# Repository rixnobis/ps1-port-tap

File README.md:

# ps1-port-tap

A pass-through for one PlayStation controller or memory card port, with every line
broken out to a 0.1" header for a logic analyser. Cut a controller extension cable in
half, solder the console half to J1 and the device half to J2, and clip the analyser
onto J3.

## Why it is wired to a cut cable

The PS1 port connector is proprietary, and I could not find a published drawing of it
I would trust. The best public source is a forum post giving a 4 mm pitch, but its
author traced the positions from a scaled photo. So this revision has no connector on
the board: J1 and J2 are 1x10 rows at
2.54 mm with 1.0 mm holes, big enough for the cable's conductors. The M2 holes beside
each row are for zip ties that hold the cable jacket. A board-mounted socket can come
in a later revision, once someone has put calipers on a real one.

## Pinout

From psx-spx, `docs/ps1/pinouts/controller-ports-and-memory-card-ports.md`. Pins 1-9
are the port pins. Pin 10 carries the cable shield straight through and is not tapped.
Memory card slots have no IRQ (pin 8) and no shield.

| Pin | Signal | | Pin | Signal |
|---|---|---|---|---|
| 1 | DAT, data from device | | 6 | /CS, port select |
| 2 | CMD, data to device | | 7 | SCK, clock |
| 3 | +7.5V, rumble supply | | 8 | /IRQ, lightgun |
| 4 | GND | | 9 | /ACK, acknowledge |
| 5 | +3.5V, logic supply | | 10 | shield |

The full table is also printed on the back silkscreen, so the cable can be wired from
the board alone.

J3 is a 2x9 header. Odd pins carry the taps (DAT, CMD, 7V5, 3V5, CS, SCK, IRQ, ACK)
and every even pin is GND, so each probe gets its own ground. The signal taps go through
100R, which keeps the analyser's lead capacitance off the bus; fit 0R if you want a
transparent tap. The two supply taps go through 10k, so a probe clipped onto a rail
cannot short it.

## Layout

Two layers, 40 x 51 mm, routed by script and every run straight. Port line n crosses
B.Cu from J1 pin n to J2 pin n. A tapped line drops through a via at its J3 column and
runs straight down F.Cu to its resistor, and on to its J3 pin. Both layers are poured
with GND, with stitching vias between the through-lines, so the copper there stays as
stitched guard ground. The pour stops at a straight edge around each pad row, because
between two header pads it can only form slivers; the GND pins inside those strips reach
the pour through traces.

`tools/check_geometry.py` checks what DRC does not. It flags any bend sharper than
45 degrees, any segment shorter than its width, any trace narrower than its net class,
any dangling end and any overlapping segment. `tools/crops.sh` renders every pad row
and the resistor row at about 4x, in `renders/crops/`.

## Files

- `ps1-port-tap.kicad_sch`, `.kicad_pcb`, `.kicad_pro`: KiCad 10 project
- `schematic.pdf`, `renders/`: every copper and silk layer, plus 3D views
- `fab/ps1-port-tap-gerbers.zip`, `fab/ps1-port-tap-bom.csv`, `fab/ps1-port-tap-cpl.csv`:
  ready for JLCPCB, with the resistors assembled and the headers hand-fitted. On the
  JLC preview, check that the resistors sit square on their pads. LCSC lists C25804 (10k)
  as out of stock right now; any 0603 10k works.

## Rebuilding

Everything is generated from the scripts in `tools/`. `tools/build.sh` runs the whole
pipeline: schematic, ERC, placement and routing through the pcbnew Python API, pours,
DRC with schematic parity, the geometry check, renders, crops and fab outputs. It stops
on any ERC, DRC or geometry finding. Requires KiCad 10 (`kicad-cli` and the `pcbnew`
Python module), `rsvg-convert` and ImageMagick.

Not yet built or tested on hardware.

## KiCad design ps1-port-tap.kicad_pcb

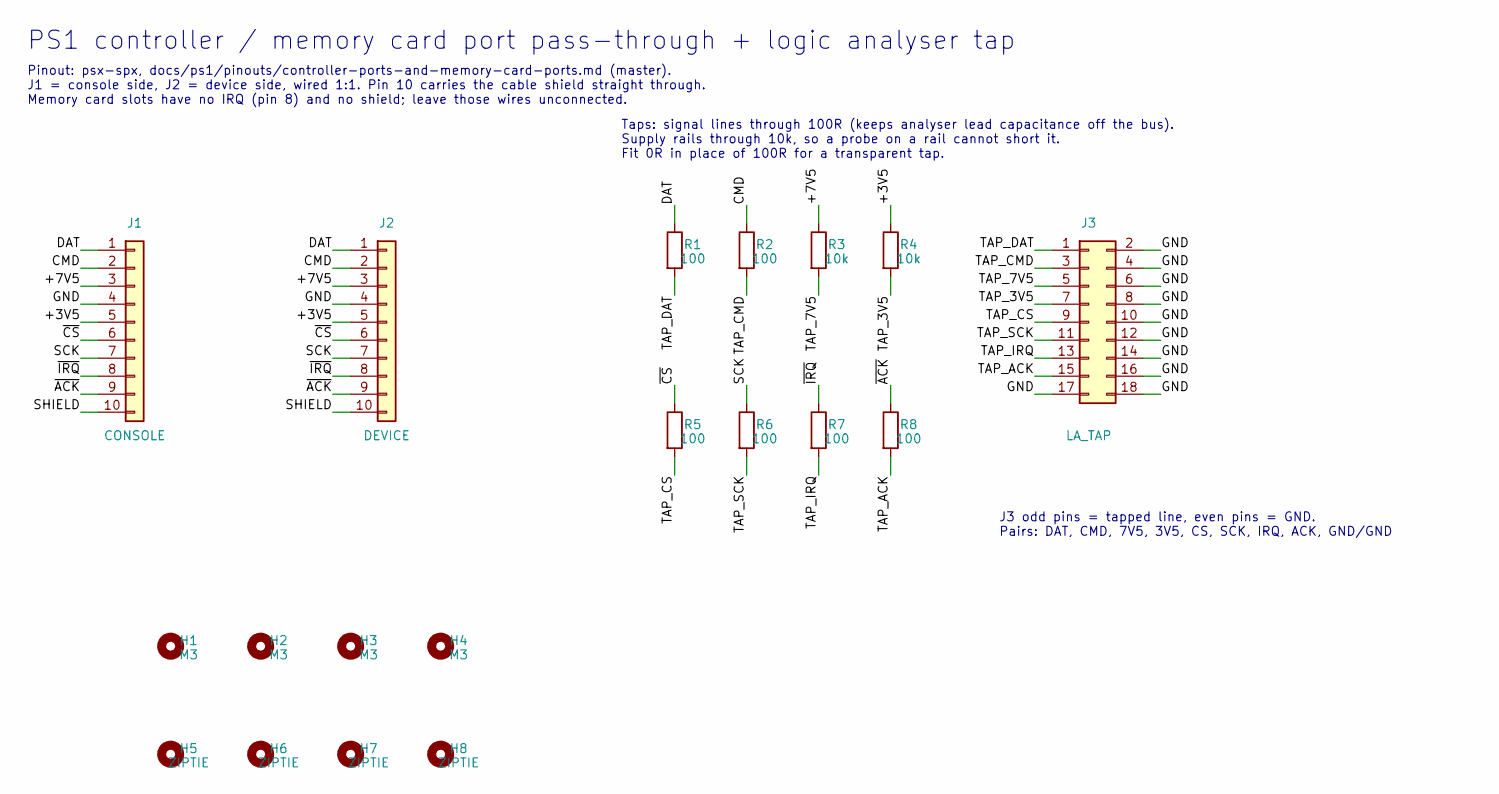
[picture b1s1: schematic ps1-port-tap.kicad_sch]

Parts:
H1, H2, H3, H4: M3; MountingHole_3.2mm_M3
H5, H6, H7, H8: ZIPTIE; MountingHole_2.2mm_M2
J1: CONSOLE; PinHeader_1x10_P2.54mm_Vertical
J2: DEVICE; PinHeader_1x10_P2.54mm_Vertical
J3: LA_TAP; PinHeader_2x09_P2.54mm_Vertical
R1, R2, R5, R6, R7, R8: 100; R_0603_1608Metric; LCSC C22775
R3, R4: 10k; R_0603_1608Metric; LCSC C25804

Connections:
/+3V5: J1.5, J2.5, R4.1
/+7V5: J1.3, J2.3, R3.1
/CMD: J1.2, J2.2, R2.1
/DAT: J1.1, J2.1, R1.1
/GND: J1.4, J2.4, J3.2, J3.4, J3.6, J3.8, J3.10, J3.12, J3.14, J3.16, J3.17, J3.18
/SCK: J1.7, J2.7, R6.1
/SHIELD: J1.10, J2.10
/TAP_3V5: J3.7, R4.2
/TAP_7V5: J3.5, R3.2
/TAP_ACK: J3.15, R8.2
/TAP_CMD: J3.3, R2.2
/TAP_CS: J3.9, R5.2
/TAP_DAT: J3.1, R1.2
/TAP_IRQ: J3.13, R7.2
/TAP_SCK: J3.11, R6.2
/~ACK: J1.9, J2.9, R8.1
/~CS: J1.6, J2.6, R5.1
/~IRQ: J1.8, J2.8, R7.1

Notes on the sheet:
PS1 controller / memory card port pass-through + logic analyser tap
Pinout: psx-spx, docs/ps1/pinouts/controller-ports-and-memory-card-ports.md (master). J1 = console side, J2 = device side, wired 1:1. Pin 10 carries the cable shield straight through. Memory card slots have no IRQ (pin 8) and no shield; leave those wires unconnected.
Taps: signal lines through 100R (keeps analyser lead capacitance off the bus). Supply rails through 10k, so a probe on a rail cannot short it. Fit 0R in place of 100R for a transparent tap.
J3 odd pins = tapped line, even pins = GND. Pairs: DAT, CMD, 7V5, 3V5, CS, SCK, IRQ, ACK, GND/GND

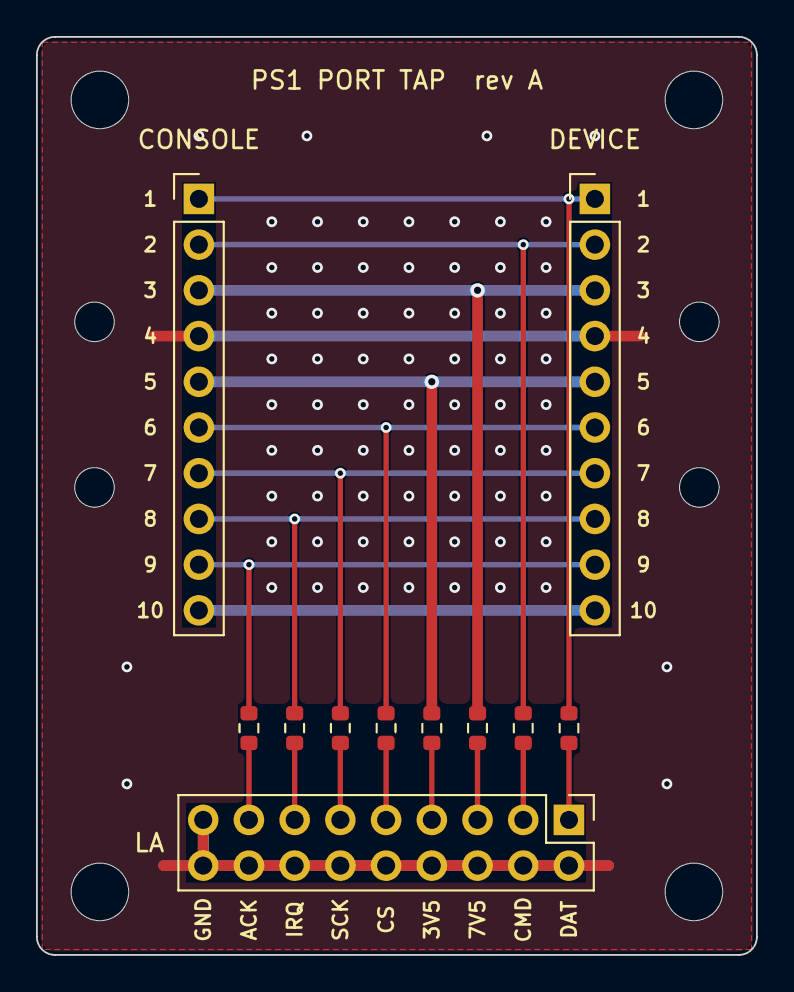
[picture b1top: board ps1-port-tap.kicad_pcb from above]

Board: 2 copper layers, 40.0 x 51.0 mm, 19 parts (0 on the bottom side), 18 nets.

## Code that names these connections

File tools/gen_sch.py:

#!/usr/bin/env python3
"""Generate ps1-port-tap.kicad_sch.

Symbols come from the stock KiCad library and are embedded in the file.
Every pin gets a short wire stub and a net label, so connectivity is carried
by label names rather than by drawn wires.
"""
import math
import re
import sys
import uuid as uuidlib
from pathlib import Path

SYMDIR = Path("/usr/share/kicad/symbols")
OUT = Path(__file__).resolve().parent.parent / "ps1-port-tap.kicad_sch"
ROOT_UUID = "6b1f3c2e-9a4d-4e57-8a0b-5f1d2c3e4a01"

# Port pinout: psx-spx, docs/ps1/pinouts/controller-ports-and-memory-card-ports.md
PORT = {
    1: "DAT",       # data from device (SIO0 RX)
    2: "CMD",       # data to device (SIO0 TX)
    3: "+7V5",      # rumble motor supply
    4: "GND",
    5: "+3V5",      # logic supply
    6: "~{CS}",     # port select
    7: "SCK",       # serial clock
    8: "~{IRQ}",    # lightgun IRQ, controller port only
    9: "~{ACK}",    # data acknowledge
    10: "SHIELD",   # cable shield, passed through, not tapped
}

# Tapped lines: (port pin, series resistor value)
TAPS = [
    (1, "100"), (2, "100"), (3, "10k"), (5, "10k"),
    (6, "100"), (7, "100"), (8, "100"), (9, "100"),
]


def uid():
    return str(uuidlib.uuid4())


def extract_symbol(lib, name):
    text = (SYMDIR / f"{lib}.kicad_sym").read_text()
    m = re.search(r'\n\t\(symbol "%s"\n' % re.escape(name), text)
    if not m:
        sys.exit(f"symbol {lib}:{name} not found")
    start = m.start() + 2  # skip "\n\t"
    depth = 0
    i = start
    in_str = False
    while True:
        c = text[i]
        if in_str:
            if c == "\\":
                i += 1
            elif c == '"':
                in_str = False
        elif c == '"':
            in_str = True
        elif c == "(":
            depth += 1
        elif c == ")":
            depth -= 1
            if depth == 0:
                break
        i += 1
    body = text[start:i + 1]
    assert body.startswith(f'(symbol "{name}"'), body[:60]
    body = body.replace(f'(symbol "{name}"', f'(symbol "{lib}:{name}"', 1)
    pins = {}
    for pm in re.finditer(
        r'\(pin \w+ \w+\s*\(at ([-\d.]+) ([-\d.]+) ([-\d.]+)\)\s*\(length [-\d.]+\)'
        r'(?:\s*\(hide yes\))?\s*\(name "[^"]*"(?:.|\n)*?\(number "([^"]+)"', body):
        x, y, a, num = float(pm[1]), float(pm[2]), float(pm[3]), pm[4]
        pins[num] = (x, y, a)
    return body, pins


LIBS = {
    "Conn_01x10": extract_symbol("Connector_Generic", "Conn_01x10"),
    "Conn_02x09_Odd_Even": extract_symbol("Connector_Generic", "Conn_02x09_Odd_Even"),
    "R": extract_symbol("Device", "R"),
    "MountingHole": extract_symbol("Mechanical", "MountingHole"),
}
LIBID = {
    "Conn_01x10": "Connector_Generic:Conn_01x10",
    "Conn_02x09_Odd_Even": "Connector_Generic:Conn_02x09_Odd_Even",
    "R": "Device:R",
    "MountingHole": "Mechanical:MountingHole",
}

items = []


def fmt(v):
    s = f"{v:.4f}".rstrip("0").rstrip(".")
    return "0" if s == "-0" else s


def place(kind, ref, value, footprint, x, y, nets, fields_extra=()):
    """nets: {pin_number: label}; a stub + label is drawn on each pin."""
    _, pins = LIBS[kind]
    su = uid()
    pin_uuids = "".join(f'\n\t\t(pin "{n}"\n\t\t\t(uuid "{uid()}")\n\t\t)' for n in pins)
    extra = "".join(
        f'\n\t\t(property "{k}" "{v}"\n\t\t\t(at {fmt(x)} {fmt(y)} 0)\n\t\t\t(effects\n\t\t\t\t(font\n\t\t\t\t\t(size 1.27 1.27)\n\t\t\t\t)\n\t\t\t\t(hide yes)\n\t\t\t)\n\t\t)'
        for k, v in fields_extra)
    in_bom = "no" if kind == "MountingHole" else "yes"
    items.append(f'''	(symbol
		(lib_id "{LIBID[kind]}")
		(at {fmt(x)} {fmt(y)} 0)
		(unit 1)
		(exclude_from_sim no)
		(in_bom {in_bom})
		(on_board yes)
		(dnp no)
		(uuid "{su}")
		(property "Reference" "{ref}"
			(at {fmt(x + (0 if kind.startswith('Conn') else 2.54))} {fmt(y - (14 if kind.startswith('Conn') else 0.8))} 0)
			(effects
				(font
					(size 1.27 1.27)
				)
			)
		)
		(property "Value" "{value}"
			(at {fmt(x + (0 if kind.startswith('Conn') else 2.54))} {fmt(y + (16 if kind.startswith('Conn') else 1.2))} 0)
			(effects
				(font
					(size 1.27 1.27)
				)
			)
		)
		(property "Footprint" "{footprint}"
			(at {fmt(x)} {fmt(y)} 0)
			(effects
				(font
					(size 1.27 1.27)
				)
				(hide yes)
			)
		)
		(property "Datasheet" ""
			(at {fmt(x)} {fmt(y)} 0)
			(effects
				(font
					(size 1.27 1.27)
				)
				(hide yes)
			)
		){extra}{pin_uuids}
		(instances
			(project "ps1-port-tap"
				(path "/{ROOT_UUID}"
					(reference "{ref}")
					(unit 1)
				)
			)
		)
	)''')
    for num, net in nets.items():
        px, py, a = pins[num]
        sx, sy = x + px, y - py                      # library y is up, sheet y is down
        dx, dy = -math.cos(math.radians(a)), math.sin(math.radians(a))
        ex, ey = sx + 2.54 * dx, sy + 2.54 * dy
        items.append(f'''	(wire
		(pts
			(xy {fmt(sx)} {fmt(sy)}) (xy {fmt(ex)} {fmt(ey)})
		)
		(stroke
			(width 0)
			(type default)
		)
		(uuid "{uid()}")
	)''')
        if abs(dx) > 0.5:
            ang, just = (180, "right") if dx < 0 else (0, "left")
        else:
            ang, just = (90, "left") if dy < 0 else (270, "right")
        items.append(f'''	(label "{net}"
		(at {fmt(ex)} {fmt(ey)} {ang})
		(effects
			(font
				(size 1.27 1.27)
			)
			(justify {just} bottom)
		)
		(uuid "{uid()}")
	)''')


def text(s, x, y, size=1.27):
    s = s.replace('"', '\\"').replace("\n", "\\n")  # no raw newlines inside a string
    items.append(f'''	(text "{s}"
		(exclude_from_sim no)
		(at {fmt(x)} {fmt(y)} 0)
		(effects
			(font
				(size {size} {size})
			)
			(justify left bottom)
		)
		(uuid "{uid()}")
	)''')


HDR1 = "Connector_PinHeader_2.54mm:PinHeader_1x10_P2.54mm_Vertical"
HDR2 = "Connector_PinHeader_2.54mm:PinHeader_2x09_P2.54mm_Vertical"
R0603 = "Resistor_SMD:R_0603_1608Metric"

place("Conn_01x10", "J1", "CONSOLE", HDR1, 40.64, 60.96, dict((str(k), v) for k, v in PORT.items()))
place("Conn_01x10", "J2", "DEVICE", HDR1, 76.2, 60.96, dict((str(k), v) for k, v in PORT.items()))

for i, (pin, val) in enumerate(TAPS):
    net = PORT[pin]
    tap = "TAP_" + re.sub(r"[~{}+]", "", net)
    place("R", f"R{i + 1}", val, R0603, 116.84 + 10.16 * (i % 4), 50.8 + 25.4 * (i // 4),
          {"1": net, "2": tap}, (("LCSC", "C22775" if val == "100" else "C25804"),))

hdr_nets = {}
for i, (pin, _) in enumerate(TAPS):
    hdr_nets[str(2 * i + 1)] = "TAP_" + re.sub(r"[~{}+]", "", PORT[pin])
    hdr_nets[str(2 * i + 2)] = "GND"
hdr_nets["17"] = "GND"
hdr_nets["18"] = "GND"
place("Conn_02x09_Odd_Even", "J3", "LA_TAP", HDR2, 175.26, 60.96, hdr_nets)

for i in range(4):
    place("MountingHole", f"H{i + 1}", "M3", "MountingHole:MountingHole_3.2mm_M3",
          45.72 + 12.7 * i, 106.68, {})
for i in range(4):
    place("MountingHole", f"H{i + 5}", "ZIPTIE", "MountingHole:MountingHole_2.2mm_M2",
          45.72 + 12.7 * i, 121.92, {})

text("PS1 controller / memory card port pass-through + logic analyser tap", 25.4, 22.86, 2.54)
text("Pinout: psx-spx, docs/ps1/pinouts/controller-ports-and-memory-card-ports.md (master).\n"
     "J1 = console side, J2 = device side, wired 1:1. Pin 10 carries the cable shield straight through.\n"
     "Memory card slots have no IRQ (pin 8) and no shield; leave those wires unconnected.", 25.4, 30.48)
text("Taps: signal lines through 100R (keeps analyser lead capacitance off the bus).\n"
     "Supply rails through 10k, so a probe on a rail cannot short it.\n"
     "Fit 0R in place of 100R for a transparent tap.", 109.22, 38.1)
text("J3 odd pins = tapped line, even pins = GND.\nPairs: DAT, CMD, 7V5, 3V5, CS, SCK, IRQ, ACK, GND/GND", 162.56, 91.44)

lib_symbols = "\n".join("\t\t" + LIBS[k][0].replace("\n", "\n\t") for k in LIBS)

OUT.write_text(f'''(kicad_sch
	(version 20260306)
	(generator "eeschema")
	(generator_version "10.0")
	(uuid "{ROOT_UUID}")
	(paper "A4")
	(title_block
		(title "ps1-port-tap")
		(rev "A")
		(company "rixnobis")
	)
	(lib_symbols
{lib_symbols}
	)
{chr(10).join(items)}
	(sheet_instances
		(path "/"
			(page "1")
		)
	)
	(embedded_fonts no)
)
''')
print("wrote", OUT)
